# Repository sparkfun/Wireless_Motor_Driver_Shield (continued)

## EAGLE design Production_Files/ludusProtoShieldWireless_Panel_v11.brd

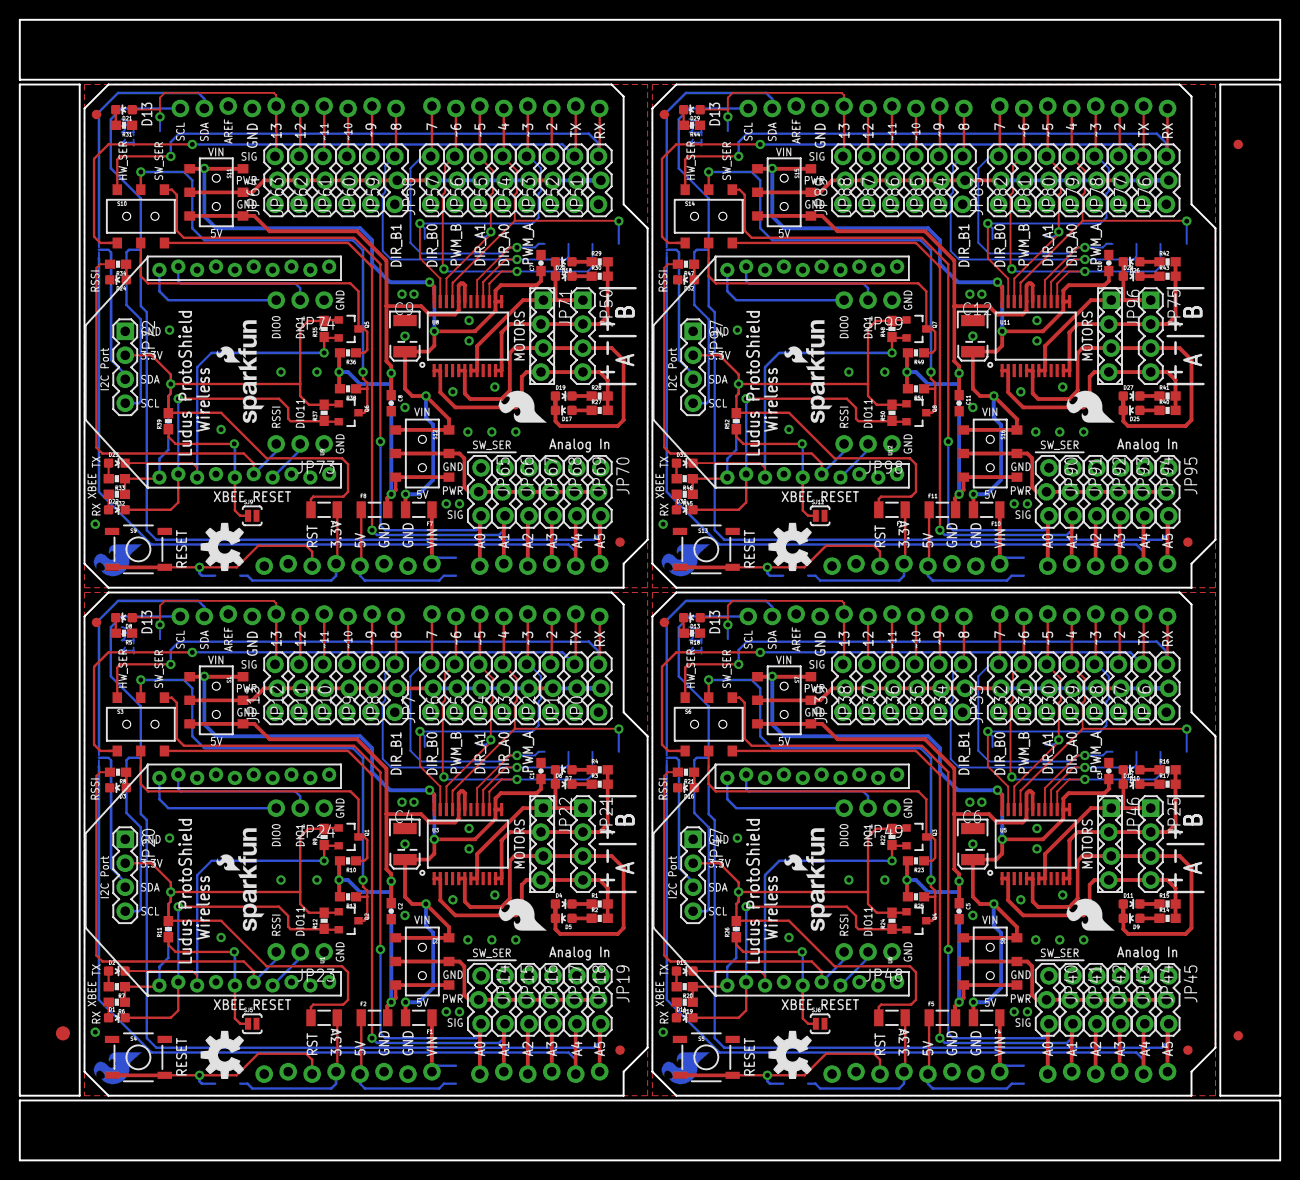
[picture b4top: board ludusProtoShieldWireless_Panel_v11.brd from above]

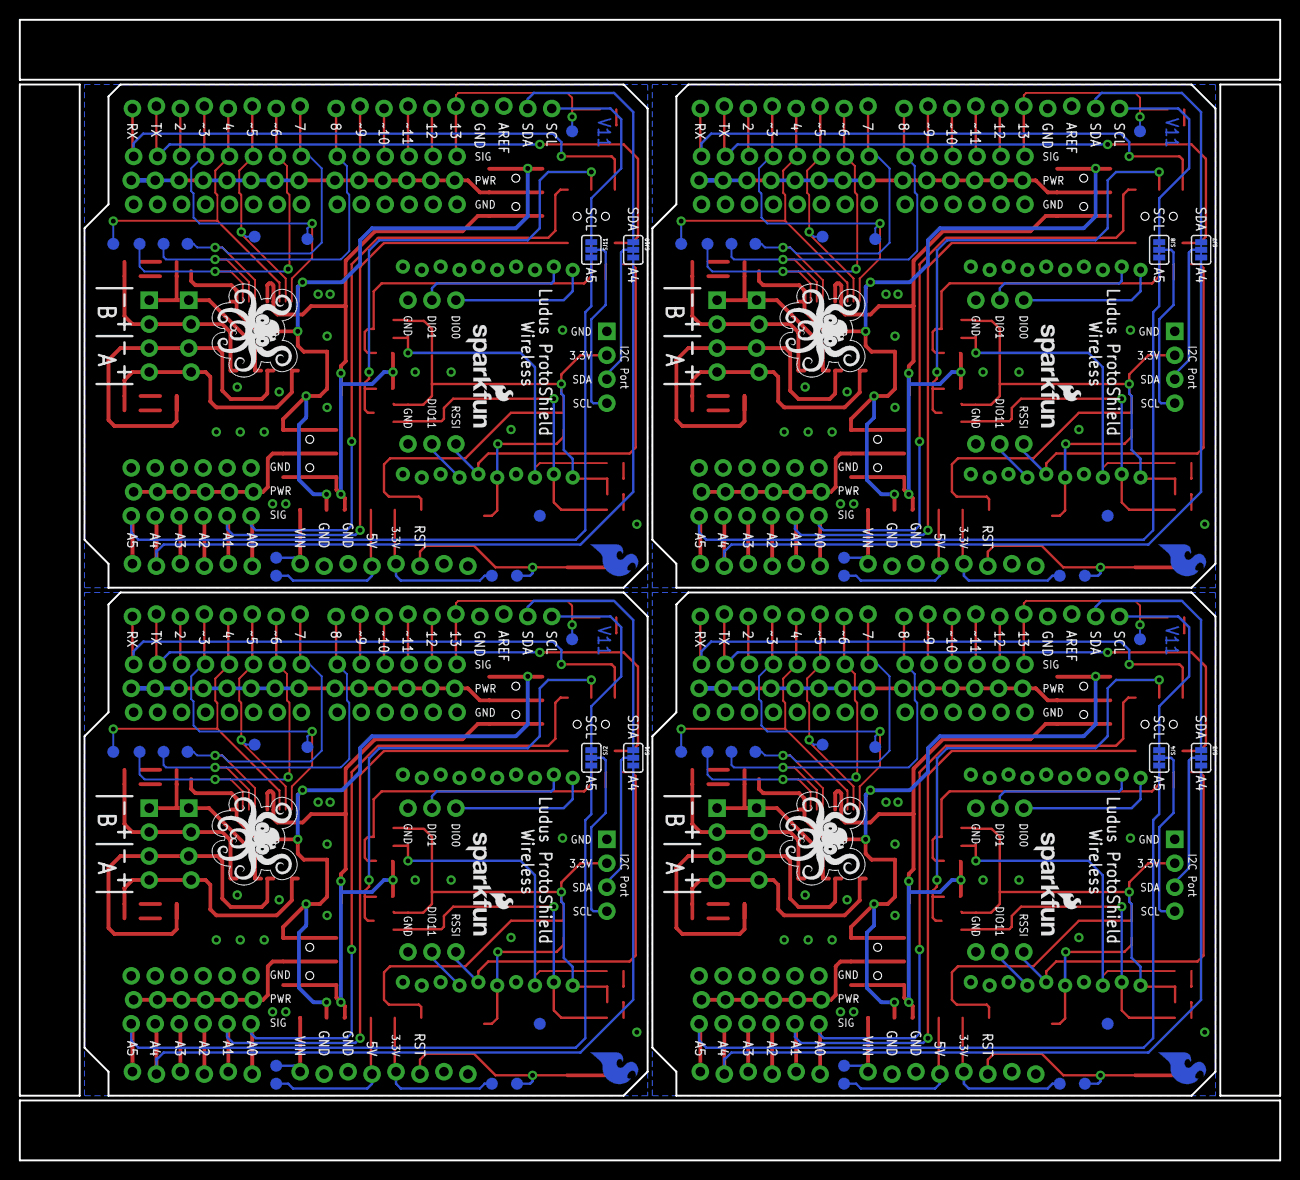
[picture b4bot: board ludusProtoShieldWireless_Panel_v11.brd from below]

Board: 2 copper layers, 133.6 x 120.9 mm, 339 parts (68 on the bottom side), 220 nets.

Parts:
C1, C2, C3, C5, C7, C8, C10, C11: 0.1uF; 0603-CAP
C4, C6, C9, C12: 10uf , 20V; EIA3528
D1, D14, D22, D30: Red; LED-0603
D2, D15, D23, D31: Green; LED-0603
D3, D5, D7, D9, D10, D16, D17, D18, D24, D25, D26, D32: Yellow; LED-0603
D4, D6, D8, D11, D12, D13, D19, D20, D21, D27, D28, D29: Blue; LED-0603
E$1: FIDUCIAL-1.5X3
E$4, E$5: FIDUCIAL-1X2
F1, F2, F3, F4, F5, F6, F7, F8, F9, F10, F11, F12: PTC-1206
FID1, FID2, FID3, FID4, FID5, FID6, FID7, FID8: FIDUCIAL1X2; FIDUCIAL-1X2
JP0, JP26, JP51, JP76: D0; 1X03_LOCK
JP1, JP27, JP52, JP77: D1; 1X03_LOCK
JP2, JP28, JP53, JP78: D2; 1X03_LOCK
JP3, JP29, JP54, JP79: D3; 1X03_LOCK
JP4, JP30, JP55, JP80: D4; 1X03_LOCK
JP5, JP31, JP56, JP81: D5; 1X03_LOCK
JP6, JP32, JP57, JP82: D6; 1X03_LOCK
JP7, JP33, JP58, JP83: D7; 1X03_LOCK
JP8, JP34, JP59, JP84: D8; 1X03_LOCK
JP9, JP35, JP60, JP85: D9; 1X03_LOCK
JP10, JP36, JP61, JP86: D10; 1X03_LOCK
JP11, JP37, JP62, JP87: D11; 1X03_LOCK
JP12, JP38, JP63, JP88: D12; 1X03_LOCK
JP13, JP39, JP64, JP89: D13; 1X03_LOCK
JP14, JP40, JP65, JP90: A0; 1X03_LOCK
JP15, JP41, JP66, JP91: A1; 1X03_LOCK
JP16, JP42, JP67, JP92: A2; 1X03_LOCK
JP17, JP43, JP68, JP93: A3; 1X03_LOCK
JP18, JP44, JP69, JP94: A4; 1X03_LOCK
JP19, JP45, JP70, JP95: A5; 1X03_LOCK
JP20, JP21, JP25, JP47, JP50, JP72, JP75, JP97: 1X04
JP22, JP46, JP71, JP96: 1X04_LOCK
JP23, JP24, JP48, JP49, JP73, JP74, JP98, JP99: 1X03_NO_SILK
LOGO1, LOGO6, LOGO11, LOGO16: OSHW-LOGOM; OSHW-LOGO-M
LOGO2, LOGO4, LOGO7, LOGO9, LOGO12, LOGO14, LOGO17, LOGO19: SFE_LOGO_NAME_FLAME.1_INCH; SFE_LOGO_NAME_FLAME_.1
LOGO3, LOGO8, LOGO13, LOGO18: SFE_LOGO_FLAME.2_INCH; SFE_LOGO_FLAME_.2
LOGO5, LOGO10, LOGO15, LOGO20: SFE_LOGO_FLAME.2COP; SFE_LOGO_FLAME_COPPER_.2
Q1, Q2, Q3, Q4, Q5, Q6, Q7, Q8: MOSFET-NCHANNELBSS138; SOT23-3
R1, R2, R3, R4, R6, R7, R8, R9, R10, R11, R12, R13, R14, R15, R16, R17, R19, R20, R21, R22, R23, R24, R25, R26, R27, R28, R29, R30, R32, R33, R34, R35, R36, R37, R38, R39, R40, R41, R42, R43, R45, R46, R47, R48, R49, R50, R51, R52: 1K; 0603-RES
R5, R18, R31, R44: 330; 0603-RES
S1, S2, S7, S8, S11, S12, S15, S16: AYZ0202
S3, S6, S10, S14: DPDT; AYZ0202
S4, S5, S9, S13: RESET; TACTILE-SWITCH-SMD
SJ1, SJ2, SJ3, SJ4, SJ7, SJ8, SJ10, SJ11: PAD-JUMPER-3-3OF3_NC_BY_TRACE_YES_SILK_FULL_BOX
SJ5, SJ6, SJ9, SJ12: SJ_2S-NO
TP1, TP2, TP3, TP4, TP5, TP6, TP7, TP8, TP9, TP10, TP11, TP12, TP13, TP14, TP15, TP16, TP17, TP18, TP19, TP20, TP21, TP22, TP23, TP24, TP25, TP26, TP27, TP28, TP29, TP30, TP31, TP32, TP33, TP34, TP35, TP36, TP37, TP38, TP39, TP40, TP41, TP42, TP43, TP44, TP45, TP46, TP47, TP48: PAD.03X.05
U1, U6, U9, U12: XBEE-1XBEE-1_LOCK; XBEE-1_LOCK
U2, U4, U7, U10: ARDUINO; UNO_R3_SHIELD_NOLABELS_LOCK
U3, U5, U8, U11: TB6612FNG; SSOP24
U$1, U$2, U$3, U$4: SFE_LUDUSSFE_LUDUS-M; SFE_LUDUS-M

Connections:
3.3V: F3.1, TP11.P$1, U2.3.3V
3.3V1: F6.1, TP23.P$1, U4.3.3V
3.3V2: F9.1, TP35.P$1, U7.3.3V
3.3V3: F12.1, TP47.P$1, U10.3.3V
5V: F2.1, TP8.P$1, U2.5V
5V1: F5.1, TP20.P$1, U4.5V
5V2: F8.1, TP32.P$1, U7.5V
5V3: F11.1, TP44.P$1, U10.5V
A0/SW_RXI: JP14.3, S3.3, U2.A0
A0/SW_RXI1: JP40.3, S6.3, U4.A0
A0/SW_RXI2: JP65.3, S10.3, U7.A0
A0/SW_RXI3: JP90.3, S14.3, U10.A0
A1: JP45.3, SJ2.3, U4.A5
A1/SW_TXO: JP15.3, S3.6, U2.A1
A1/SW_TXO1: JP41.3, S6.6, U4.A1
A1/SW_TXO2: JP66.3, S10.6, U7.A1
A1/SW_TXO3: JP91.3, S14.6, U10.A1
A2: JP16.3, U2.A2
A3: JP17.3, U2.A3
A4: JP18.3, SJ3.3, U2.A4
A5: JP19.3, SJ4.3, U2.A5
A6: JP44.3, SJ1.3, U4.A4
A7: JP42.3, U4.A2
A8: JP43.3, U4.A3
A9: JP70.3, SJ8.3, U7.A5
A10: JP69.3, SJ7.3, U7.A4
A11: JP67.3, U7.A2
A12: JP68.3, U7.A3
A13: JP95.3, SJ11.3, U10.A5
A14: JP94.3, SJ10.3, U10.A4
A15: JP92.3, U10.A2
A16: JP93.3, U10.A3
AIN1: JP4.3, TP1.P$1, U2.D4, U3.21
AIN2: JP5.3, TP2.P$1, U2.D5, U3.22
AIN3: JP31.3, TP14.P$1, U4.D5, U5.22
AIN4: JP30.3, TP13.P$1, U4.D4, U5.21
AIN5: JP56.3, TP26.P$1, U7.D5, U8.22
AIN6: JP55.3, TP25.P$1, U7.D4, U8.21
AIN7: JP81.3, TP38.P$1, U10.D5, U11.22
AIN8: JP80.3, TP37.P$1, U10.D4, U11.21
ANALOG_PWR_RAIL: JP14.2, JP15.2, JP16.2, JP17.2, JP18.2, JP19.2, S2.2, S2.5
ANALOG_PWR_RAIL1: JP40.2, JP41.2, JP42.2, JP43.2, JP44.2, JP45.2, S8.2, S8.5
ANALOG_PWR_RAIL2: JP65.2, JP66.2, JP67.2, JP68.2, JP69.2, JP70.2, S12.2, S12.5
ANALOG_PWR_RAIL3: JP90.2, JP91.2, JP92.2, JP93.2, JP94.2, JP95.2, S16.2, S16.5
AOUT1: JP21.4, JP22.4, R1.2, R2.2, U3.1, U3.2
AOUT2: D4.A, D5.C, JP21.3, JP22.3, U3.5, U3.6
AOUT3: JP25.4, JP46.4, R14.2, R15.2, U5.1, U5.2
AOUT4: D9.C, D11.A, JP25.3, JP46.3, U5.5, U5.6
AOUT5: JP50.4, JP71.4, R27.2, R28.2, U8.1, U8.2
AOUT6: D17.C, D19.A, JP50.3, JP71.3, U8.5, U8.6
AOUT7: JP75.4, JP96.4, R40.2, R41.2, U11.1, U11.2
AOUT8: D25.C, D27.A, JP75.3, JP96.3, U11.5, U11.6
BIN1: JP7.3, TP4.P$1, U2.D7, U3.17
BIN2: JP8.3, TP5.P$1, U2.D8, U3.16
BIN3: JP33.3, TP16.P$1, U4.D7, U5.17
BIN4: JP34.3, TP17.P$1, U4.D8, U5.16
BIN5: JP58.3, TP28.P$1, U7.D7, U8.17
BIN6: JP59.3, TP29.P$1, U7.D8, U8.16
BIN7: JP83.3, TP40.P$1, U10.D7, U11.17
BIN8: JP84.3, TP41.P$1, U10.D8, U11.16
BOUT1: JP21.2, JP22.2, R3.2, R4.2, U3.11, U3.12
BOUT2: D6.A, D7.C, JP21.1, JP22.1, U3.7, U3.8
BOUT3: D10.C, D12.A, JP25.1, JP46.1, U5.7, U5.8
BOUT4: JP25.2, JP46.2, R16.2, R17.2, U5.11, U5.12
BOUT5: D18.C, D20.A, JP50.1, JP71.1, U8.7, U8.8
BOUT6: JP50.2, JP71.2, R29.2, R30.2, U8.11, U8.12
BOUT7: D26.C, D28.A, JP75.1, JP96.1, U11.7, U11.8
BOUT8: JP75.2, JP96.2, R42.2, R43.2, U11.11, U11.12
D0/RXI: JP0.3, S3.1, U2.RX
D0/RXI1: JP26.3, S6.1, U4.RX
D0/RXI2: JP51.3, S10.1, U7.RX
D0/RXI3: JP76.3, S14.1, U10.RX
D1: JP38.3, U4.D12
D1/TXO: JP1.3, S3.4, U2.TX
D1/TXO1: JP27.3, S6.4, U4.TX
D1/TXO2: JP52.3, S10.4, U7.TX
D1/TXO3: JP77.3, S14.4, U10.TX
D2: JP2.3, U2.D2
D3: D13.A, JP39.3, TP19.P$1, U4.D13
D4: JP36.3, U4.D10
D5: JP28.3, U4.D2
D6: JP37.3, U4.D11
D7: JP35.3, U4.D9
D8: JP63.3, U7.D12
D9: JP9.3, U2.D9
D10: JP10.3, U2.D10
D11: JP11.3, U2.D11
D12: JP12.3, U2.D12
D13: D8.A, JP13.3, TP7.P$1, U2.D13
D14: D21.A, JP64.3, TP31.P$1, U7.D13
D15: JP61.3, U7.D10
D16: JP53.3, U7.D2
D17: JP62.3, U7.D11
D18: JP60.3, U7.D9
D19: JP88.3, U10.D12
D20: D29.A, JP89.3, TP43.P$1, U10.D13
D21: JP86.3, U10.D10
D22: JP78.3, U10.D2
D23: JP87.3, U10.D11
D24: JP85.3, U10.D9
DIN: D2.C, Q1.2, R9.1, U1.3
DIN1: D15.C, Q3.2, R22.1, U6.3
DIN2: D23.C, Q5.2, R35.1, U9.3
DIN3: D31.C, Q7.2, R48.1, U12.3
DIO0: JP24.3, U1.20
DIO1: JP24.2, U1.19
DIO2: JP48.2, U6.7
DIO3: JP49.3, U6.20
DIO4: JP49.2, U6.19
DIO5: JP73.2, U9.7
DIO6: JP74.3, U9.20
DIO7: JP74.2, U9.19
DIO8: JP98.2, U12.7
DIO9: JP99.3, U12.20
DIO10: JP99.2, U12.19
DIO11: JP23.2, U1.7
DOUT: D1.C, Q2.2, R12.1, U1.2
DOUT1: D14.C, Q4.2, R24.1, U6.2
DOUT2: D22.C, Q6.2, R37.1, U9.2
DOUT3: D30.C, Q8.2, R50.1, U12.2
FUSED_3.3V: F3.2, JP20.2, Q1.1, Q2.1, R6.1, R7.1, R9.2, R11.2, R12.2, U1.1
FUSED_3.3V1: F6.2, JP47.2, Q3.1, Q4.1, R19.1, R20.1, R22.2, R24.2, R26.2, U6.1
FUSED_3.3V2: F9.2, JP72.2, Q5.1, Q6.1, R32.1, R33.1, R35.2, R37.2, R39.2, U9.1
FUSED_3.3V3: F12.2, JP97.2, Q7.1, Q8.1, R45.1, R46.1, R48.2, R50.2, R52.2, U12.1
FUSED_5V: C2.1, F2.2, R10.2, R13.2, S1.3, S1.6, S2.3, S2.6, U3.19, U3.20
FUSED_5V1: C5.1, F5.2, R23.2, R25.2, S7.3, S7.6, S8.3, S8.6, U5.19, U5.20
FUSED_5V2: C8.1, F8.2, R36.2, R38.2, S11.3, S11.6, S12.3, S12.6, U8.19, U8.20
FUSED_5V3: C11.1, F11.2, R49.2, R51.2, S15.3, S15.6, S16.3, S16.6, U11.19, U11.20
FUSED_VIN: C1.1, C4.A, F1.2, S1.1, S1.4, S2.1, S2.4, U3.13, U3.14, U3.24
FUSED_VIN1: C3.1, C6.A, F4.2, S7.1, S7.4, S8.1, S8.4, U5.13, U5.14, U5.24
FUSED_VIN2: C7.1, C9.A, F7.2, S11.1, S11.4, S12.1, S12.4, U8.13, U8.14, U8.24
FUSED_VIN3: C10.1, C12.A, F10.2, S15.1, S15.4, S16.1, S16.4, U11.13, U11.14, U11.24
GND: C1.2, C2.2, C4.C, D3.C, JP0.1, JP1.1, JP2.1, JP3.1, JP4.1, JP5.1, JP6.1, JP7.1, JP8.1, JP9.1, JP10.1, JP11.1, JP12.1, JP13.1, JP14.1, JP15.1, JP16.1, JP17.1, JP18.1, JP19.1, JP20.1, JP23.1, JP24.1, R5.1, S4.1, S4.2, SJ5.2, TP9.P$1, U1.10, U2.GND@0, U2.GND@1, U2.GND@2, U3.3, U3.4, U3.9, U3.10, U3.18
GND1: C3.2, C5.2, C6.C, D16.C, JP26.1, JP27.1, JP28.1, JP29.1, JP30.1, JP31.1, JP32.1, JP33.1, JP34.1, JP35.1, JP36.1, JP37.1, JP38.1, JP39.1, JP40.1, JP41.1, JP42.1, JP43.1, JP44.1, JP45.1, JP47.1, JP48.1, JP49.1, R18.1, S5.1, S5.2, SJ6.2, TP21.P$1, U4.GND@0, U4.GND@1, U4.GND@2, U5.3, U5.4, U5.9, U5.10, U5.18, U6.10
GND2: C7.2, C8.2, C9.C, D24.C, JP51.1, JP52.1, JP53.1, JP54.1, JP55.1, JP56.1, JP57.1, JP58.1, JP59.1, JP60.1, JP61.1, JP62.1, JP63.1, JP64.1, JP65.1, JP66.1, JP67.1, JP68.1, JP69.1, JP70.1, JP72.1, JP73.1, JP74.1, R31.1, S9.1, S9.2, SJ9.2, TP33.P$1, U7.GND@0, U7.GND@1, U7.GND@2, U8.3, U8.4, U8.9, U8.10, U8.18, U9.10
GND3: C10.2, C11.2, C12.C, D32.C, JP76.1, JP77.1, JP78.1, JP79.1, JP80.1, JP81.1, JP82.1, JP83.1, JP84.1, JP85.1, JP86.1, JP87.1, JP88.1, JP89.1, JP90.1, JP91.1, JP92.1, JP93.1, JP94.1, JP95.1, JP97.1, JP98.1, JP99.1, R44.1, S13.1, S13.2, SJ12.2, TP45.P$1, U10.GND@0, U10.GND@1, U10.GND@2, U11.3, U11.4, U11.9, U11.10, U11.18, U12.10
unnamed: D8.C, R5.2
unnamed: D9.A, R14.1
unnamed: D5.A, R2.1
unnamed: D11.C, R15.1
unnamed: D4.C, R1.1
unnamed: D7.A, R4.1
unnamed: D6.C, R3.1
unnamed: D10.A, R16.1
unnamed: D12.C, R17.1
unnamed: D13.C, R18.2
unnamed: D14.A, R19.2
unnamed: D15.A, R20.2
unnamed: D16.A, R21.1
unnamed: D17.A, R27.1
unnamed: D19.C, R28.1
unnamed: D18.A, R29.1
unnamed: D20.C, R30.1
unnamed: D21.C, R31.2
unnamed: D22.A, R32.2
unnamed: D1.A, R6.2
unnamed: D23.A, R33.2
unnamed: D24.A, R34.1
unnamed: D25.A, R40.1
unnamed: D27.C, R41.1
unnamed: D26.A, R42.1
unnamed: D28.C, R43.1
unnamed: D29.C, R44.2
unnamed: D30.A, R45.2
unnamed: D31.A, R46.2
unnamed: D32.A, R47.1
unnamed: D2.A, R7.2
unnamed: D3.A, R8.1
PWMA: JP3.3, TP3.P$1, U2.D3, U3.23
PWMA1: JP29.3, TP15.P$1, U4.D3, U5.23
PWMA2: JP54.3, TP27.P$1, U7.D3, U8.23
PWMA3: JP79.3, TP39.P$1, U10.D3, U11.23
PWMB: JP6.3, TP6.P$1, U2.D6, U3.15
PWMB1: JP32.3, TP18.P$1, U4.D6, U5.15
PWMB2: JP57.3, TP30.P$1, U7.D6, U8.15
PWMB3: JP82.3, TP42.P$1, U10.D6, U11.15
PWR_RAIL: JP0.2, JP1.2, JP2.2, JP3.2, JP4.2, JP5.2, JP6.2, JP7.2, JP8.2, JP9.2, JP10.2, JP11.2, JP12.2, JP13.2, S1.2, S1.5
PWR_RAIL1: JP26.2, JP27.2, JP28.2, JP29.2, JP30.2, JP31.2, JP32.2, JP33.2, JP34.2, JP35.2, JP36.2, JP37.2, JP38.2, JP39.2, S7.2, S7.5
PWR_RAIL2: JP51.2, JP52.2, JP53.2, JP54.2, JP55.2, JP56.2, JP57.2, JP58.2, JP59.2, JP60.2, JP61.2, JP62.2, JP63.2, JP64.2, S11.2, S11.5
PWR_RAIL3: JP76.2, JP77.2, JP78.2, JP79.2, JP80.2, JP81.2, JP82.2, JP83.2, JP84.2, JP85.2, JP86.2, JP87.2, JP88.2, JP89.2, S15.2, S15.5
RESET: S4.3, S4.4, TP12.P$1, U2.RES
RESET1: S5.3, S5.4, TP24.P$1, U4.RES
RESET2: S9.3, S9.4, TP36.P$1, U7.RES
RESET3: S13.3, S13.4, TP48.P$1, U10.RES
RSSI: JP23.3, R8.2, U1.6
RSSI1: JP48.3, R21.2, U6.6
RSSI2: JP73.3, R34.2, U9.6
RSSI3: JP98.3, R47.2, U12.6
SCL: SJ4.1, U2.SCL
SCL1: SJ2.1, U4.SCL
SCL2: SJ8.1, U7.SCL
SCL3: SJ11.1, U10.SCL
SCL_I2C_PORT: JP20.4, SJ4.2
SCL_I2C_PORT1: JP47.4, SJ2.2
SCL_I2C_PORT2: JP72.4, SJ8.2
SCL_I2C_PORT3: JP97.4, SJ11.2
SDA: SJ3.1, U2.SDA
SDA1: SJ1.1, U4.SDA
SDA2: SJ7.1, U7.SDA
SDA3: SJ10.1, U10.SDA
SDA_I2C_PORT: JP20.3, SJ3.2
SDA_I2C_PORT1: JP47.3, SJ1.2
SDA_I2C_PORT2: JP72.3, SJ7.2
SDA_I2C_PORT3: JP97.3, SJ10.2
VIN: F1.1, TP10.P$1, U2.VIN
VIN1: F4.1, TP22.P$1, U4.VIN
VIN2: F7.1, TP34.P$1, U7.VIN
VIN3: F10.1, TP46.P$1, U10.VIN
XBEE_RESET: R11.1, SJ5.1, U1.5
XBEE_RESET1: R26.1, SJ6.1, U6.5
XBEE_RESET2: R39.1, SJ9.1, U9.5
XBEE_RESET3: R52.1, SJ12.1, U12.5
XBEE_RXI: Q2.3, R13.1, S3.2
XBEE_RXI1: Q4.3, R25.1, S6.2
XBEE_RXI2: Q6.3, R38.1, S10.2
XBEE_RXI3: Q8.3, R51.1, S14.2
XBEE_TXO: Q1.3, R10.1, S3.5
XBEE_TXO1: Q3.3, R23.1, S6.5
XBEE_TXO2: Q5.3, R36.1, S10.5
XBEE_TXO3: Q7.3, R49.1, S14.5

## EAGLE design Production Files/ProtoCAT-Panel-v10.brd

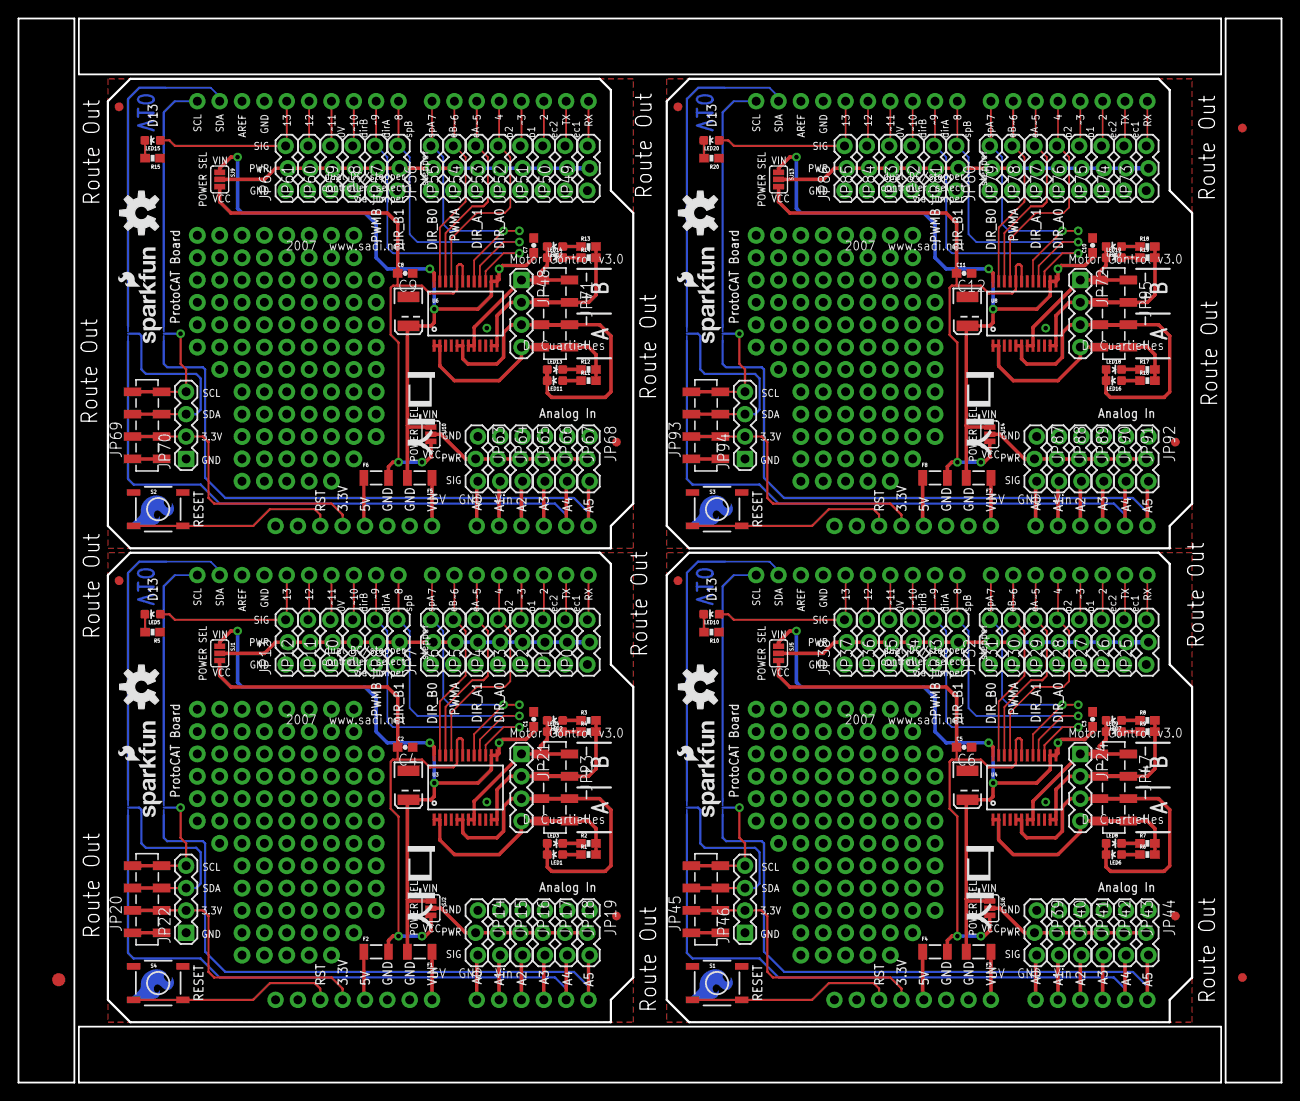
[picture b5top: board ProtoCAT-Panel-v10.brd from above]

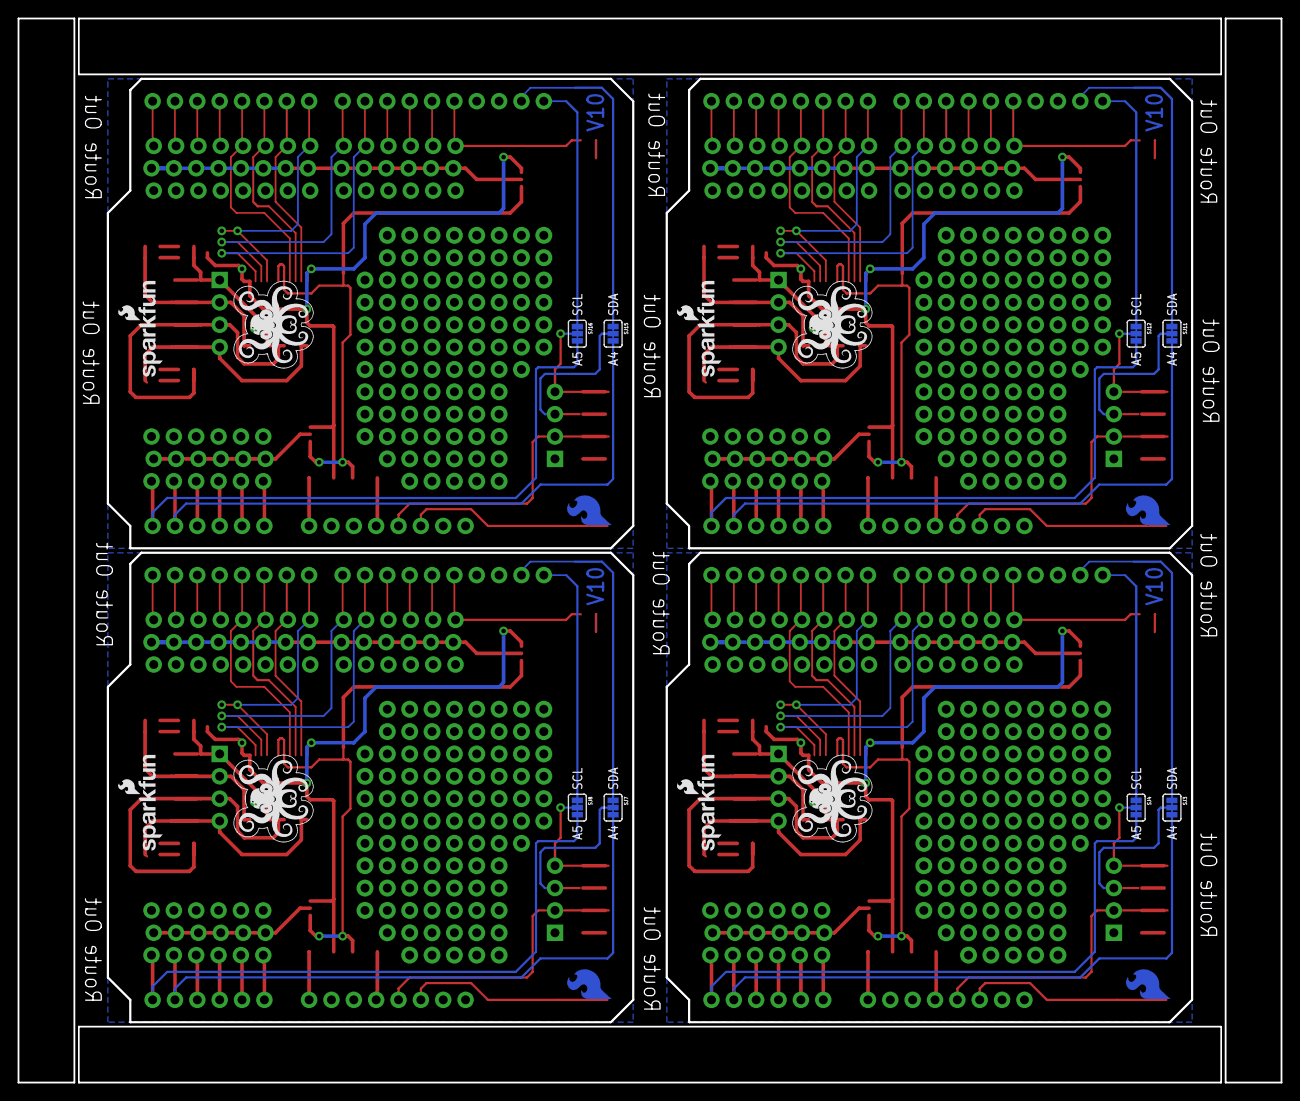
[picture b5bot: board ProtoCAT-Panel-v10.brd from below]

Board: 2 copper layers, 143.5 x 120.9 mm, 215 parts (16 on the bottom side), 168 nets.

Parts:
C1, C2, C3, C5, C7, C8, C10, C11: 0.1uF; 0603-CAP
C4, C6, C9, C12: 10uf , 20V; EIA3528
E$1: FIDUCIAL-1.5X3
E$2, E$3: FIDUCIAL-1X2
F1, F2, F3, F4, F5, F6, F7, F8: PTCSMD; PTC-1206
FID1, FID2, FID3, FID4, FID5, FID6, FID7, FID8: FIDUCIAL1X2; FIDUCIAL-1X2
JP0, JP25, JP49, JP73: D0; 1X03_LOCK
JP1, JP26, JP50, JP74: D1; 1X03_LOCK
JP2, JP27, JP51, JP75: D2; 1X03_LOCK
JP3, JP28, JP52, JP76: D3; 1X03_LOCK
JP4, JP29, JP53, JP77: D4; 1X03_LOCK
JP5, JP30, JP54, JP78: D5; 1X03_LOCK
JP6, JP31, JP55, JP79: D6; 1X03_LOCK
JP7, JP32, JP56, JP80: D7; 1X03_LOCK
JP8, JP33, JP57, JP81: D8; 1X03_LOCK
JP9, JP34, JP58, JP82: D9; 1X03_LOCK
JP10, JP35, JP59, JP83: D10; 1X03_LOCK
JP11, JP36, JP60, JP84: D11; 1X03_LOCK
JP12, JP37, JP61, JP85: D12; 1X03_LOCK
JP13, JP38, JP62, JP86: D13; 1X03_LOCK
JP14, JP39, JP63, JP87: A0; 1X03_LOCK
JP15, JP40, JP64, JP88: A1; 1X03_LOCK
JP16, JP41, JP65, JP89: A2; 1X03_LOCK
JP17, JP42, JP66, JP90: A3; 1X03_LOCK
JP18, JP43, JP67, JP91: A4; 1X03_LOCK
JP19, JP44, JP68, JP92: A5; 1X03_LOCK
JP20, JP23, JP45, JP47, JP69, JP71, JP93, JP95: 1X04_SMD_STRAIGHT_COMBO
JP21, JP22, JP24, JP46, JP48, JP70, JP72, JP94: 1X04
LED1, LED2, LED6, LED7, LED11, LED12, LED16, LED17: Yellow; LED-0603
LED3, LED4, LED5, LED8, LED9, LED10, LED13, LED14, LED15, LED18, LED19, LED20: Blue; LED-0603
LOGO1, LOGO5, LOGO9, LOGO13: OSHW-LOGOM; OSHW-LOGO-M
LOGO2, LOGO4, LOGO6, LOGO8, LOGO10, LOGO12, LOGO14, LOGO16: SFE_LOGO_NAME_FLAME.1_INCH; SFE_LOGO_NAME_FLAME_.1
LOGO3, LOGO7, LOGO11, LOGO15: SFE_LOGO_FLAME.2COP; SFE_LOGO_FLAME_COPPER_.2
R1, R2, R3, R4, R6, R7, R8, R9, R11, R12, R13, R14, R16, R17, R18, R19: 1k; 0603-RES
R5, R10, R15, R20: 330; 0603-RES
S1, S2, S3, S4: RESET; TACTILE-SWITCH-SMD
SJ1, SJ2, SJ5, SJ6, SJ9, SJ10, SJ13, SJ14: JUMPER-PAD-3-2OF3_NC_BY_PASTE; PAD-JUMPER-3-2OF3_NC_BY_PASTE_YES_SILK_FULL_BOX
SJ3, SJ4, SJ7, SJ8, SJ11, SJ12, SJ15, SJ16: PAD-JUMPER-3-3OF3_NC_BY_TRACE_YES_SILK_FULL_BOX
U1, U2, U5, U7: ARDUINO; UNO_R3_SHIELD_NOLABELS
U3, U4, U6, U8: TB6612FNG; SSOP24
U$1, U$2, U$3, U$4: SFE_LUDUS; SFE_LUDUS-M

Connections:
3.3V: JP20.2, JP22.2, U1.3.3V
3.3V1: JP45.2, JP46.2, U2.3.3V
3.3V2: JP69.2, JP70.2, U5.3.3V
3.3V3: JP93.2, JP94.2, U7.3.3V
A0: JP14.3, U1.A0
A1: JP15.3, U1.A1
A2: JP16.3, U1.A2
A3: JP17.3, U1.A3
A4: JP18.3, SJ3.3, U1.A4
A5: JP19.3, SJ4.3, U1.A5
A6: JP44.3, SJ8.3, U2.A5
A7: JP43.3, SJ7.3, U2.A4
A8: JP41.3, U2.A2
A9: JP40.3, U2.A1
A10: JP39.3, U2.A0
A11: JP42.3, U2.A3
A12: JP68.3, SJ12.3, U5.A5
A13: JP67.3, SJ11.3, U5.A4
A14: JP65.3, U5.A2
A15: JP64.3, U5.A1
A16: JP63.3, U5.A0
A17: JP66.3, U5.A3
A18: JP92.3, SJ16.3, U7.A5
A19: JP91.3, SJ15.3, U7.A4
A20: JP89.3, U7.A2
A21: JP88.3, U7.A1
A22: JP87.3, U7.A0
A23: JP90.3, U7.A3
AIN1: JP4.3, U1.D4, U3.21
AIN2: JP5.3, U1.D5, U3.22
AIN3: JP30.3, U2.D5, U4.22
AIN4: JP29.3, U2.D4, U4.21
AIN5: JP54.3, U5.D5, U6.22
AIN6: JP53.3, U5.D4, U6.21
AIN7: JP78.3, U7.D5, U8.22
AIN8: JP77.3, U7.D4, U8.21
ANALOG_PWR_RAIL: JP14.2, JP15.2, JP16.2, JP17.2, JP18.2, JP19.2, SJ2.2
ANALOG_PWR_RAIL1: JP39.2, JP40.2, JP41.2, JP42.2, JP43.2, JP44.2, SJ6.2
ANALOG_PWR_RAIL2: JP63.2, JP64.2, JP65.2, JP66.2, JP67.2, JP68.2, SJ10.2
ANALOG_PWR_RAIL3: JP87.2, JP88.2, JP89.2, JP90.2, JP91.2, JP92.2, SJ14.2
AOUT1: JP21.4, JP23.4, R1.2, R2.2, U3.1, U3.2
AOUT2: JP21.3, JP23.3, LED1.C, LED3.A, U3.5, U3.6
AOUT3: JP24.4, JP47.4, R6.2, R7.2, U4.1, U4.2
AOUT4: JP24.3, JP47.3, LED6.C, LED8.A, U4.5, U4.6
AOUT5: JP48.4, JP71.4, R11.2, R12.2, U6.1, U6.2
AOUT6: JP48.3, JP71.3, LED11.C, LED13.A, U6.5, U6.6
AOUT7: JP72.4, JP95.4, R16.2, R17.2, U8.1, U8.2
AOUT8: JP72.3, JP95.3, LED16.C, LED18.A, U8.5, U8.6
BIN1: JP7.3, U1.D7, U3.17
BIN2: JP32.3, U2.D7, U4.17
BIN3: JP56.3, U5.D7, U6.17
BIN4: JP80.3, U7.D7, U8.17
BOUT1: JP21.2, JP23.2, R3.2, R4.2, U3.11, U3.12
BOUT2: JP21.1, JP23.1, LED2.C, LED4.A, U3.7, U3.8
BOUT3: JP24.1, JP47.1, LED7.C, LED9.A, U4.7, U4.8
BOUT4: JP24.2, JP47.2, R8.2, R9.2, U4.11, U4.12
BOUT5: JP48.1, JP71.1, LED12.C, LED14.A, U6.7, U6.8
BOUT6: JP48.2, JP71.2, R13.2, R14.2, U6.11, U6.12
BOUT7: JP72.1, JP95.1, LED17.C, LED19.A, U8.7, U8.8
BOUT8: JP72.2, JP95.2, R18.2, R19.2, U8.11, U8.12
D0: JP0.3, U1.RX
D1: JP1.3, U1.TX
D2: JP2.3, U1.D2
D3: JP3.3, U1.D3
D4: JP37.3, U2.D12
D5: JP38.3, LED10.A, U2.D13
D6: JP35.3, U2.D10
D7: JP27.3, U2.D2
D8: JP36.3, U2.D11
D9: JP25.3, U2.RX
D10: JP10.3, U1.D10
D11: JP11.3, U1.D11
D12: JP12.3, U1.D12
D13: JP13.3, LED5.A, U1.D13
D14: JP26.3, U2.TX
D15: JP28.3, U2.D3
D16: JP61.3, U5.D12
D17: JP62.3, LED15.A, U5.D13
D18: JP59.3, U5.D10
D19: JP51.3, U5.D2
D20: JP60.3, U5.D11
D21: JP49.3, U5.RX
D22: JP50.3, U5.TX
D23: JP52.3, U5.D3
D24: JP85.3, U7.D12
D25: JP86.3, LED20.A, U7.D13
D26: JP83.3, U7.D10
D27: JP75.3, U7.D2
D28: JP84.3, U7.D11
D29: JP73.3, U7.RX
D30: JP74.3, U7.TX
D31: JP76.3, U7.D3
FUSED_VCC: C2.1, F2.2, SJ1.3, SJ2.3, U3.19, U3.20
FUSED_VCC1: C5.1, F4.2, SJ5.3, SJ6.3, U4.19, U4.20
FUSED_VCC2: C8.1, F6.2, SJ9.3, SJ10.3, U6.19, U6.20
FUSED_VCC3: C11.1, F8.2, SJ13.3, SJ14.3, U8.19, U8.20
FUSED_VIN: C1.1, C4.A, F1.2, SJ1.1, SJ2.1, U3.13, U3.14, U3.24
FUSED_VIN1: C3.1, C6.A, F3.2, SJ5.1, SJ6.1, U4.13, U4.14, U4.24
FUSED_VIN2: C7.1, C9.A, F5.2, SJ9.1, SJ10.1, U6.13, U6.14, U6.24
FUSED_VIN3: C10.1, C12.A, F7.2, SJ13.1, SJ14.1, U8.13, U8.14, U8.24
GND: C1.2, C2.2, C4.C, JP0.1, JP1.1, JP2.1, JP3.1, JP4.1, JP5.1, JP6.1, JP7.1, JP8.1, JP9.1, JP10.1, JP11.1, JP12.1, JP13.1, JP14.1, JP15.1, JP16.1, JP17.1, JP18.1, JP19.1, JP20.1, JP22.1, R5.1, S4.1, S4.2, U1.GND@0, U1.GND@1, U1.GND@2, U3.3, U3.4, U3.9, U3.10, U3.18
GND1: C3.2, C5.2, C6.C, JP25.1, JP26.1, JP27.1, JP28.1, JP29.1, JP30.1, JP31.1, JP32.1, JP33.1, JP34.1, JP35.1, JP36.1, JP37.1, JP38.1, JP39.1, JP40.1, JP41.1, JP42.1, JP43.1, JP44.1, JP45.1, JP46.1, R10.1, S1.1, S1.2, U2.GND@0, U2.GND@1, U2.GND@2, U4.3, U4.4, U4.9, U4.10, U4.18
GND2: C7.2, C8.2, C9.C, JP49.1, JP50.1, JP51.1, JP52.1, JP53.1, JP54.1, JP55.1, JP56.1, JP57.1, JP58.1, JP59.1, JP60.1, JP61.1, JP62.1, JP63.1, JP64.1, JP65.1, JP66.1, JP67.1, JP68.1, JP69.1, JP70.1, R15.1, S2.1, S2.2, U5.GND@0, U5.GND@1, U5.GND@2, U6.3, U6.4, U6.9, U6.10, U6.18
GND3: C10.2, C11.2, C12.C, JP73.1, JP74.1, JP75.1, JP76.1, JP77.1, JP78.1, JP79.1, JP80.1, JP81.1, JP82.1, JP83.1, JP84.1, JP85.1, JP86.1, JP87.1, JP88.1, JP89.1, JP90.1, JP91.1, JP92.1, JP93.1, JP94.1, R20.1, S3.1, S3.2, U7.GND@0, U7.GND@1, U7.GND@2, U8.3, U8.4, U8.9, U8.10, U8.18
unnamed: LED5.C, R5.2
unnamed: LED1.A, R1.1
unnamed: LED3.C, R2.1
unnamed: LED2.A, R3.1
unnamed: LED4.C, R4.1
unnamed: JP8.3, U1.D8, U3.16
unnamed: LED6.A, R6.1
unnamed: LED8.C, R7.1
unnamed: LED7.A, R8.1
unnamed: LED9.C, R9.1
unnamed: LED10.C, R10.2
unnamed: JP33.3, U2.D8, U4.16
unnamed: LED11.A, R11.1
unnamed: LED13.C, R12.1
unnamed: LED12.A, R13.1
unnamed: LED14.C, R14.1
unnamed: LED15.C, R15.2
unnamed: JP57.3, U5.D8, U6.16
unnamed: LED16.A, R16.1
unnamed: LED18.C, R17.1
unnamed: LED17.A, R18.1
unnamed: LED19.C, R19.1
unnamed: LED20.C, R20.2
unnamed: JP81.3, U7.D8, U8.16
PWMA: JP6.3, U1.D6, U3.23
PWMA1: JP31.3, U2.D6, U4.23
PWMA2: JP55.3, U5.D6, U6.23
PWMA3: JP79.3, U7.D6, U8.23
PWMB: JP9.3, U1.D9, U3.15
PWMB1: JP34.3, U2.D9, U4.15
PWMB2: JP58.3, U5.D9, U6.15
PWMB3: JP82.3, U7.D9, U8.15
PWR_RAIL: JP0.2, JP1.2, JP2.2, JP3.2, JP4.2, JP5.2, JP6.2, JP7.2, JP8.2, JP9.2, JP10.2, JP11.2, JP12.2, JP13.2, SJ1.2
PWR_RAIL1: JP25.2, JP26.2, JP27.2, JP28.2, JP29.2, JP30.2, JP31.2, JP32.2, JP33.2, JP34.2, JP35.2, JP36.2, JP37.2, JP38.2, SJ5.2
PWR_RAIL2: JP49.2, JP50.2, JP51.2, JP52.2, JP53.2, JP54.2, JP55.2, JP56.2, JP57.2, JP58.2, JP59.2, JP60.2, JP61.2, JP62.2, SJ9.2
PWR_RAIL3: JP73.2, JP74.2, JP75.2, JP76.2, JP77.2, JP78.2, JP79.2, JP80.2, JP81.2, JP82.2, JP83.2, JP84.2, JP85.2, JP86.2, SJ13.2
RESET: S4.3, S4.4, U1.RES
RESET1: S1.3, S1.4, U2.RES
RESET2: S2.3, S2.4, U5.RES
RESET3: S3.3, S3.4, U7.RES
SCL: SJ4.1, U1.SCL
SCL1: SJ8.1, U2.SCL
SCL2: SJ12.1, U5.SCL
SCL3: SJ16.1, U7.SCL
SCL_I2C_PORT: JP20.4, JP22.4, SJ4.2
SCL_I2C_PORT1: JP45.4, JP46.4, SJ8.2
SCL_I2C_PORT2: JP69.4, JP70.4, SJ12.2
SCL_I2C_PORT3: JP93.4, JP94.4, SJ16.2
SDA: SJ3.1, U1.SDA
SDA1: SJ7.1, U2.SDA
SDA2: SJ11.1, U5.SDA
SDA3: SJ15.1, U7.SDA
SDA_I2C_PORT: JP20.3, JP22.3, SJ3.2
SDA_I2C_PORT1: JP45.3, JP46.3, SJ7.2
SDA_I2C_PORT2: JP69.3, JP70.3, SJ11.2
SDA_I2C_PORT3: JP93.3, JP94.3, SJ15.2
VCC: F2.1, U1.5V
VCC1: F4.1, U2.5V
VCC2: F6.1, U5.5V
VCC3: F8.1, U7.5V
VIN: F1.1, U1.VIN
VIN1: F3.1, U2.VIN
VIN2: F5.1, U5.VIN
VIN3: F7.1, U7.VIN

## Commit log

2014-08-18 Initial Commit
    Initial board files
2014-08-18 Updates per - engineering review mtg 8/18
    added prototyping area
    added cut/solder jumpers for A4/A5 SDA/SCL lines for Leo
    added ~PWM labels on pins 3, 5, 6, 9, 10, 11
2014-08-19 Updated a few aesthetic elements on bottom side
    Included Ludus and sparkfun logo on bottom layer
2014-09-03 Updated fuse to 1206 part on Vcc Line
2014-10-03 Removed unused layers
    Removed unused layers and backup b# / s# files
2014-10-15 Revert "Removed unused layers"
    This reverts commit cac16d64a0abcda8bb8dc176f65466555645d099.
2014-10-16 Moved 4 pin SMD headers to Motor Driver
    Tied STDBY pin on motor driver to Vcc, added 4 pin SMD header to motor
    Driver output, and changed 3-pin headers to locking headers
2014-10-16 Removed unused layers on board
    Removed unused middle layers of board and cleaned up silkscreen artwork
    on Ludus Logo
2014-10-28 Final board changes -- ready for reds
    Moved I2C header down to account for panelizer, moved a the cut jumpers
    for A4/A5 & SCL/SDA on bottom trace
2014-10-28 Updated version to v10
    Final updates with silk changes, version number, and repo clean-up.
2014-10-28 created panel v10
2014-11-18 Initial Commit
    Updated / Changed ProtoCAT to include an XBee header
2014-12-05 Updated XBee footprint and added RESET control
    Added RESET for XBee and fixed PWR lines to the XBee
2014-12-05 Final clean-up
    Removed unused layers.
2014-12-06 Numerous minor edits
2014-12-09 clean-up - removed excess files
    removed extra board files and production panel
2015-01-08 Switched TX / RX lines on XBee
    Fixed the Switched TX / RX lines from XBee to Arduino on the HW Serial
    lines.
    Moved the thru-hole mounts for the Motors to below the SMD mount.
    Fixed LEDs for RSSI, DIN / DOUT
2015-01-08 Changed the Silkscreen name to Ludus Wireless Shield
2015-01-08 Added break-out for 4 I/O pins on XBee
    Added breakout pins for DIO0, DIO1, P0, P1 and GND to the board.
2015-01-09 Updated Silk
    Added additional silk to show the SW Serial connection on the shield
2015-01-15 Updated shield footprint to include staggered / locking holes
    * changed filenames to ludusProtoShieldWireless
    * repo name will change after this commit
2015-02-09 Updated to fix all issues -
    Also added a switch to shield for switching between VIN and 5V
2015-02-10 Approved all errors / warnings on ERC
2015-02-10 Updated all issues in SCH.
    Also, replaced the switch for the DPDT package.
2015-02-10 Fixed 2 GND flags and SJ5
    Updated nets on SJ5 and GND flags
2015-02-10 Updating board to include measures and line up silk
    Updating board file
2015-02-10 Spaced out LEDs / Resistors
    Fixed D1 / DOUT break and spaced out LEDs from resistors
2015-02-11 Airwire on R7 fixed.
2015-03-02 Minor Silk changes
    Changed the silk on the I2C port so that a rt angle connector does not
    block the pin descriptors.
    Also changed the DIN / DOUT text on the XBee to RX / TX respectively
    from the radio's point of view.
2015-03-02 Added labels to bSilk layer
    Added pin labels to bSilk
2015-03-05 Updates to final v1.0
    Ready for reds. Reviewed by Engineering.
2015-03-30 Updated for QC issues for Reds
2015-03-30 Moved test points around away from selective soldering points
    Moved testpoints around away from selective soldering points.
2015-03-31 Updated silk images
    Updated all silk images using Pete's new artwork. Bumped test point away
    from header field
2015-04-13 Moved PWM pins to 3 and 6 instead of 6 and 9
    Changed the PWM control pins on the shield to pins 3 & 6 so that it is
    compatible / does not conflict with the Arduino Servo library.
    No test points moved. Updated silk accordingly.
2015-04-13 Updated version to 1.1
2015-04-14 Updates re: Issue #4
    Fixed labels on LED7 to D1.
    Bumped the HW /SW Serial switch over to avoid the silk
2015-04-16 deleted bad panel
2015-05-19 created panel v11
2015-07-10 Cephalopod Gripe
    I removed the redundant phrase ", 8-legged (tenacled)" from the sentence explaning what Ludus is. He's an octopus, 8 is right there in the name. Also, generally speaking, octopi have 8 arms, not tent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
2015-07-10 Added Example Firmware
2015-07-30 Updating README, adding LICENSE.md file
2017-04-26 Made changes for v12 protos
2017-04-26 Updated after self Eng Design Rules Check
2017-05-02 Added new monster voltage select circuit to servo power rail
2017-05-02 Added fiducials, cleaned up silk, added staking vias
2017-05-03 Added GND symbol for test point
2017-05-31 Added female I2C header. Added manual selector switch for VIN/VS with new barrel jack to power motors separately.
2017-06-01 Added staking vias to barrel jack. Added header PTH for VS.
2017-06-02 Moved silkscreen board name up a skosh to avoid via.
2017-06-19 Changed to v14. Changed switch labels to VMOTOR
2017-06-20 Changed switches silk and added arrows in silk to show what switches do
2017-06-20 Moved silk arrow down a skosh
2017-06-23 Updated LED, RES, and CAP libraries to remove silk under parts
2017-06-26 panel
2017-08-17 Fixed README to go live
2017-08-17 Fixed title in README
